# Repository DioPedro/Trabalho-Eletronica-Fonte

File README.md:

# **Trabalho Eletrônica Fonte**
## **SSC0180 - Eletrônica para a Computação - Prof Simões** [GitHub](https://github.com/simoesusp)
--------
## **Trabalho desenvolvido pelos alunos:**
- **Diógenes Silva Pedro (Dio) - nUSP: 11883476** - [GitHub](https://github.com/DioUSP)
- **Rodrigo Lopes Assaf (Árabe) - nUSP: 11795530** - [GitHub](https://github.com/Roassaf)
- **Pedro Liduino do Nascimento (Rio) - nUSP: 11796847** - [GitHub](https://github.com/pedronii)
--------
# **Desenvolvimento:**
O intuito do projeto é desenvolver uma fonte elétrica que transforma a partir da tomada (no nosso caso 127V - corrente alteranada) em uma tensão que não seja prejudicial ao nosso circuito, tal tensão está entre 3 e 12 Volts em corrente contínua.
## **Imagem do Circuito:**
## 
## **Link para o circuito no [Falstad](http://tinyurl.com/yd8hsnw7)** 
--------
| **Componente** | **Especificações** | **Valor(Unitário)** |
|:---------------:|:-------------:|:---------------:|
|Transformador | 15V e 300mA | [R$26,00](https://produto.mercadolivre.com.br/MLB-802952898-transformador-primario-0110-0110-secundario-015v-300ma-_JM?matt_tool=82322591&matt_word&gclid=EAIaIQobChMIhsubx8z_6QIVjoSRCh005QUsEAkYCiABEgKHK_D_BwE&quantity=1) |
|4x Diodo | 400V e 3A | [R$0,38](https://www.autoeletronica.net/produtos/diodo-retificador-1n5404) |
|Diodo Zener | 1W e 15V | [R$0,18](https://www.autoeletronica.net/produtos/diodo-zener-1n4744a-15v-1w) |
|Capacitor | 1mF | [R$2,87](https://produto.mercadolivre.com.br/MLB-1499835576-capacitor-eletrolitico-1mf-x-400v-kit-c10-pcs-_JM?quantity=1#position=1&type=item&tracking_id=fa215f29-9e58-4df8-935f-7aea9beaf1e2) |
|Potenciômetro | 5kΩ | [R$1,52](https://www.americanas.com.br/produto/212584212/potenciometro-linear-5k-16mm-eixo-estriado?WT.srch=1&acc=e789ea56094489dffd798f86ff51c7a9&epar=bp_pl_00_go_inf-aces_acessorios_geral_gmv&gclid=EAIaIQobChMIlqedgtb_6QIVwoORCh24ZwAEEAkYAiABEgI6w_D_BwE&i=5d712b2d49f937f6250d8225&o=5d6e754f6c28a3cb50909602&opn=YSMESP&sellerid=10428528000110) |
|Resistência | 330Ω | [R$0,13](https://produto.mercadolivre.com.br/MLB-1342907792-resistor-330-ohms-100-unidades-_JM?quantity=1#position=1&type=item&tracking_id=64df90b6-86bd-4de3-8a9f-d59c6ad031f4) |
|Resistência | 2.2kΩ | [R$4,00](https://www.sotudo.com.br/produto/resistor-1w-2-2k-ohms) |
|Resistência | 1.1kΩ | [R$0,08](https://www.baudaeletronica.com.br/resistor-1k1-5-1-4w.html) |
|Switch | 250V e 3A | [R$8,00](https://produto.mercadolivre.com.br/MLB-1300399738-boto-chave-gangorra-mini-interruptor-liga-desliga-on-off-10x15mm-kcd13-101-3a-250v-arduino-_JM?variation=42249952649&quantity=1#reco_item_pos=0&reco_backend=machinalis-seller-items-pdp&reco_backend_type=low_level&reco_client=vip-seller_items-above&reco_id=3b5ba658-e897-4edb-bdb5-659b62db67cc) |
|Transistor | 45V e 500mA | [R$0,17](https://www.baudaeletronica.com.br/transistor-npn-bc337.html) |
|LED | 3V~3.3V | [R$0,24](https://www.baudaeletronica.com.br/led-de-alto-brilho-branco.html) |
|Custo Total | | **R$44,71** |
--------
#### Obs: Os links dos produtos estão disponíveis ao clicar no preço
--------
## **Justificativa dos componentes escolhidos:**
1. **Transformador**:
    * Transforma a corrente alternada com 127V em uma corrente, ainda alternada, de 17V, assim ficamos mais próximos da tensão de entre 3 e 12V desejada.
2. **Ponte Retificadora**:
    * Transforma a corrente alternada com ~17V em uma corrente contínua com ~16V com ~342 nA.
3. **Capacitor**:
    * O intuito do capacitor é guardar corrente e com isso liberá-la quando necessário para o circuito. Como queremos manter a tensão máxima o mais próximo possível de 12V, usaremos um capacitor de 1 micro Faraday. 
4. **Diodo Zener**:
    * Equivale a ~6mA e ~13V, temos P = i.u -> P = 0,006 * 13 -> P = 0,78W -> P = 780 mW, então um diodo de 1W se faz suficiente.
    * Estamos usando ele inversamente polarizado, qualquer diodo que seja polazirado inversamente funciona praticamente não conduzindo corrente elétrica desde que não ultrapasse a tensão de ruptura, que é a tensão máxima, no nosso caso 13V. 
5. **Potenciômetro**:
    * Resistor variável que controla qual a tensão atual no circuito e a corrente, no nosso caso temos um mínimo de ~3V e ~25mA e um máximo de ~12.2V e ~101mA. 
6. **Resistência**:
    * 330Ω: Limita a corrente que passa pelo Zener, cujo qual não pode ter uma potência maior que 1W ou uma tensão maior que 13V.
    * 1.1kΩ: Usado para ajustar a corrente e tensão que chega no LED, caso não tivessemos esse resistor o LED acabaria queimando.
    * 2.2kΩ: Ajuda a regular a tensão de base que volta ao transistor e consequentemente a voltagem final do circuito.
7. **Transistor**:
    * Transistor NPN BC337, usado para controlar corrente elétrica, barrando ou amplificando a corrente, no nosso caso adequamos a corrente que vai para o potênciometro. 
8. **LED**:
    * Demonstar que o circuito está ligado ou desligado.
9. **Switch**:
    * Ligar e desligar o circuito.
--------
# Projeto do Esquemático:
## 
# PCB (Printed Circuit Board) no Eagle:
## 
#### Os arquivos originais se encontram no repositório
--------
# Video explicativo:
## 
--------
# Agradecimentos:
Agradecer ao Professor Simões por mesmo em tempos difíceis como os atuais estar se esforçando para o decorrer da disciplina. O grupo espera que tudo esteja bem e espera que assim que possível possa voltar a reencontrar o professor presencialmente pelo Campus ou no ICMC.

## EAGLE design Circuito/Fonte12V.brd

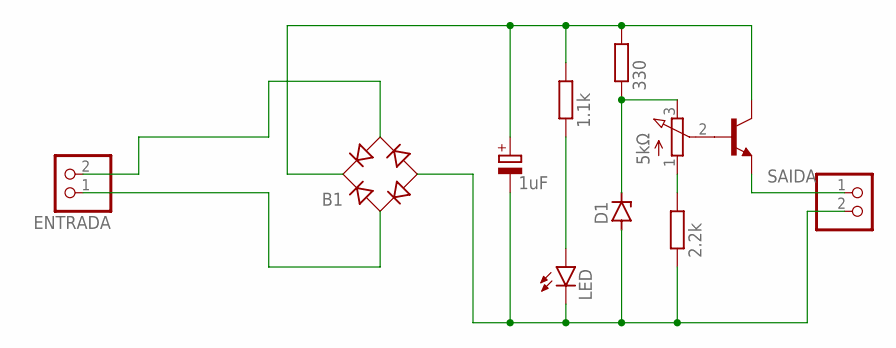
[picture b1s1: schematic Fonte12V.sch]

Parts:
B1: RB1A
C1: 1uF; E2,5-6E
D1: ZENER-DIODEDO41Z10; DO41Z10
ENTRADA: PINHD-1X2; 1X02
LED: TLLR4400; LED3MM
R1: 1.1k; 0207/10
R2: 5kΩ; 3RP/1610N
R3: 2.2k; 0207/10
R4: 330; 0207/10
SAIDA: PINHD-1X2; 1X02
T1: 2N706; TO18

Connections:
unnamed: B1.+, C1.+, R1.2, R4.2, T1.3 (C)
unnamed: B1.-, C1.-, D1.A, LED.K (C), R3.1, SAIDA.2
unnamed: B1.AC1, ENTRADA.1
unnamed: R2.2 (S), T1.2 (B)
unnamed: R2.1 (A), R3.2
unnamed: SAIDA.1, T1.1 (E)
unnamed: D1.C, R2.3 (E), R4.1
unnamed: B1.AC2, ENTRADA.2
unnamed: LED.A, R1.1

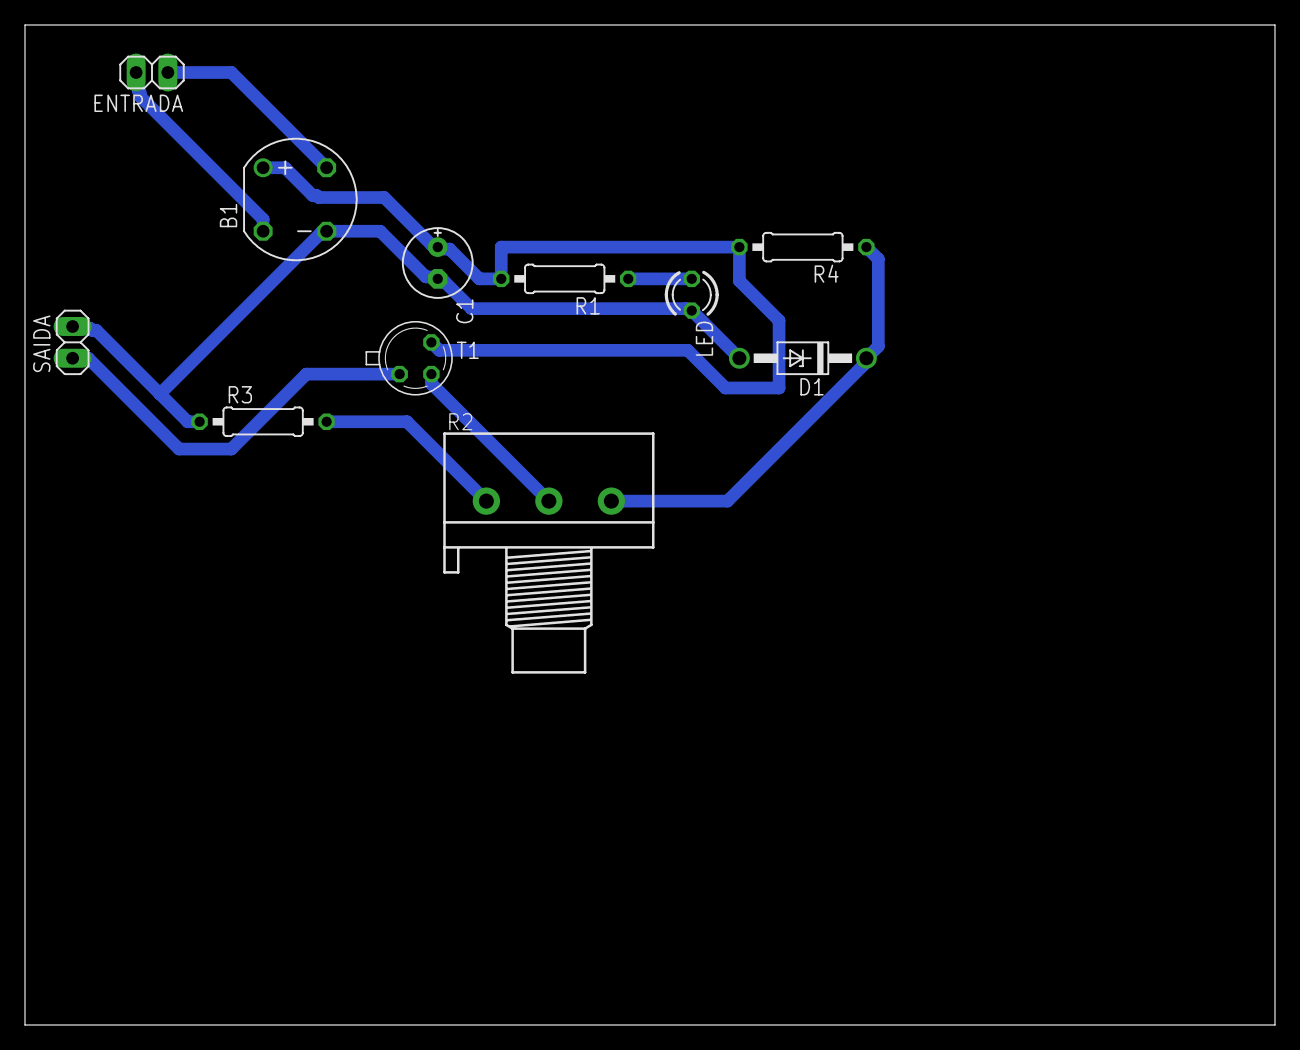
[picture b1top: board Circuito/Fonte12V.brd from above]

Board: 2 copper layers, 100.0 x 80.0 mm, 11 parts (0 on the bottom side), 9 nets.

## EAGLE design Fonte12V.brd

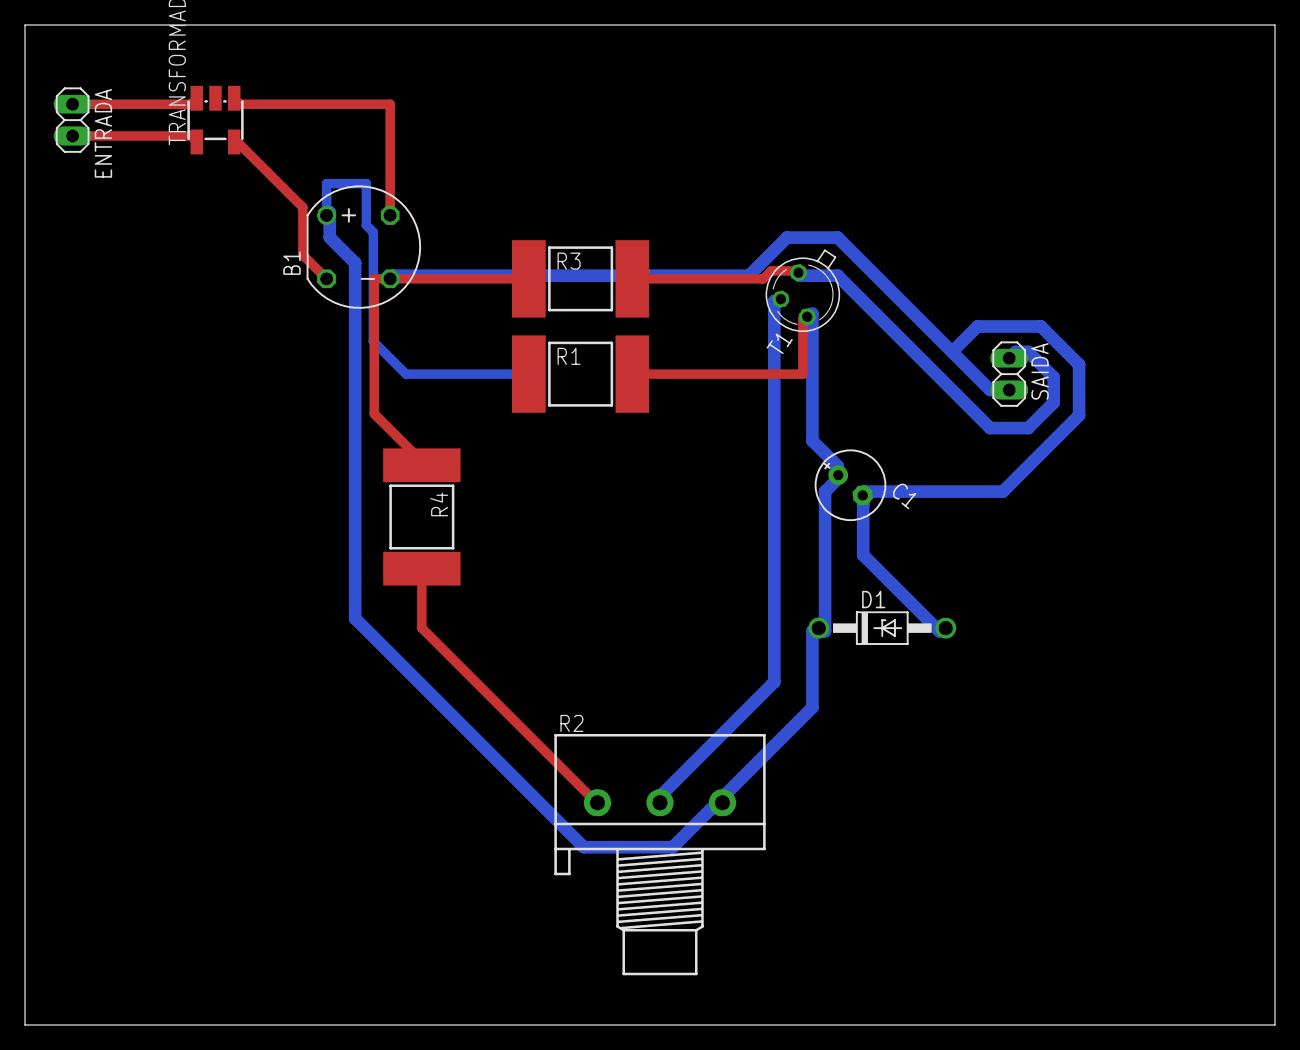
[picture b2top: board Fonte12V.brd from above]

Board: 2 copper layers, 100.0 x 80.0 mm, 11 parts (0 on the bottom side), 9 nets.

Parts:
B1: RB1A
C1: 1uF; E2,5-6E
D1: DO41Z10
ENTRADA: 1X02
R1: 330Ω; BVS
R2: 5kΩ; 3RP/1610N
R3: 120Ω; BVS
R4: 2kΩ; BVS
SAIDA: 1X02
T1: 2N706; TO18
TRANSFORMADOR: SM-T4

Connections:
unnamed: B1.+, C1.+, D1.C, R1.1, R1.2, R2.3, T1.3
unnamed: B1.-, C1.-, D1.A, R3.1, R4.1, SAIDA.2
unnamed: ENTRADA.1, TRANSFORMADOR.2
unnamed: R2.2, T1.2
unnamed: R2.1, R4.2
unnamed: R3.2, SAIDA.1, T1.1
unnamed: B1.AC2, TRANSFORMADOR.5
unnamed: ENTRADA.2, TRANSFORMADOR.1
unnamed: B1.AC1, TRANSFORMADOR.4

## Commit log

2020-06-12 Atualizando o readme
2020-06-13 Testes com o README
2020-06-13 Readme
